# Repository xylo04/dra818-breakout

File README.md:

# DRA818 Breakout

This KiCad project is a breakout board for the DRA818 VHF/UHF transceiver
module. It's extremely simple and designed to be used on a breadboard. It does
incorporate an SMA antenna connector.

This fits the Dorji DRA818 module, both the UHF and VHF variants, and also the
pin-compatible NiceRF SA818 VHF and UHF modules.

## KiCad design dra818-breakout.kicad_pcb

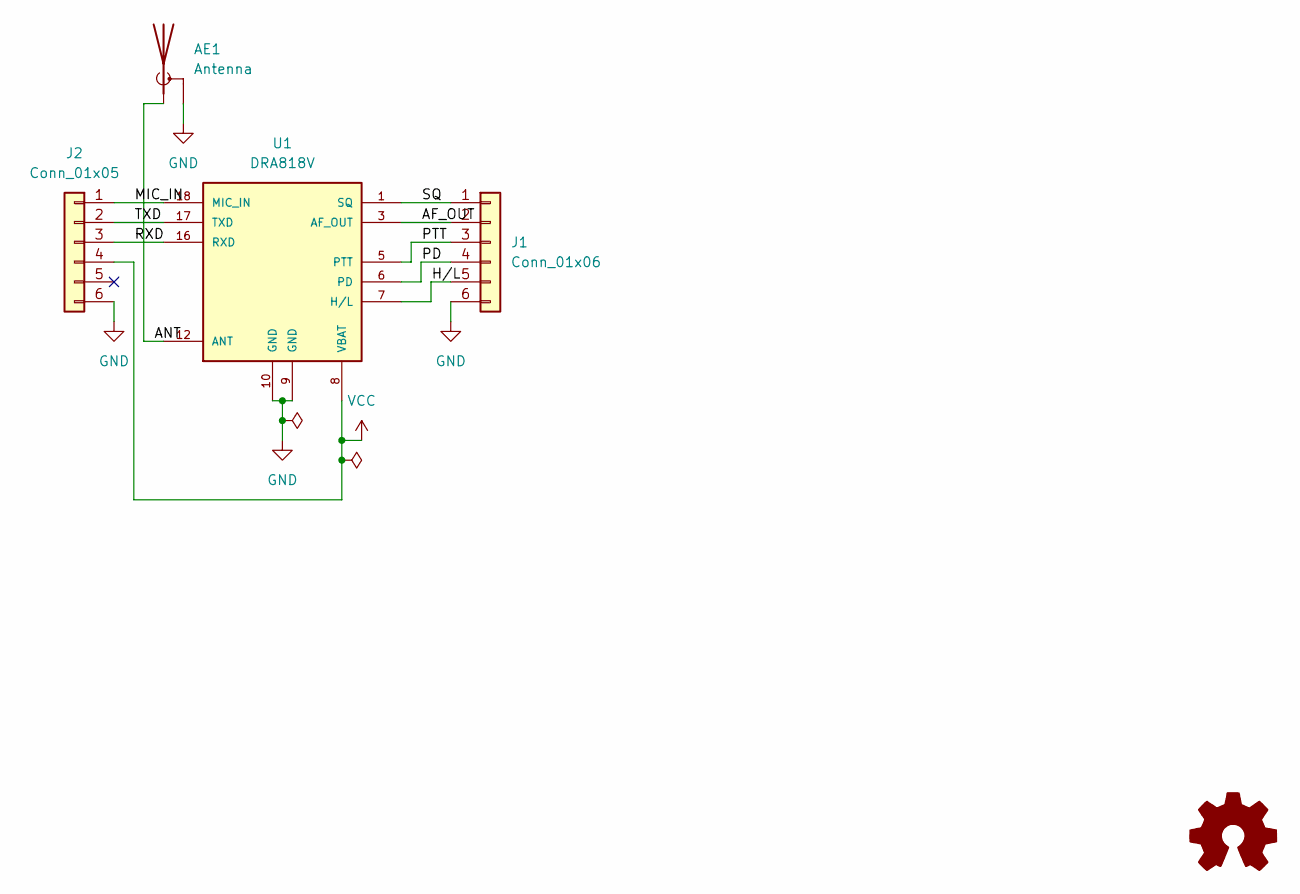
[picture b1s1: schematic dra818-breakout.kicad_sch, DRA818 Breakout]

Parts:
AE1: Antenna; SMA_Molex_73251-1153_EdgeMount_Horizontal
J1: Conn_01x06; PinHeader_1x06_P2.54mm_Vertical
J2: Conn_01x05; PinHeader_1x06_P2.54mm_Vertical
SYM1: Logo_Open_Hardware_Small; OSHW-Logo2_7.3x6mm_SilkScreen
U1: DRA818V; DORJI_DRA818V; PART_REV 1.23

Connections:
/AF_OUT: J1.2, U1.3 (AF_OUT)
/ANT: AE1.1 (A), U1.12 (ANT)
/H/L: J1.5, U1.7 (H/L)
/MIC_IN: J2.1, U1.18 (MIC_IN)
/PD: J1.4, U1.6 (PD)
/PTT: J1.3, U1.5 (PTT)
/RXD: J2.3, U1.16 (RXD)
/SQ: J1.1, U1.1 (SQ)
/TXD: J2.2, U1.17 (TXD)
GND: AE1.2 (Shield), J1.6, J2.6, U1.9 (GND), U1.10 (GND)
VCC: J2.4, U1.8 (VBAT)

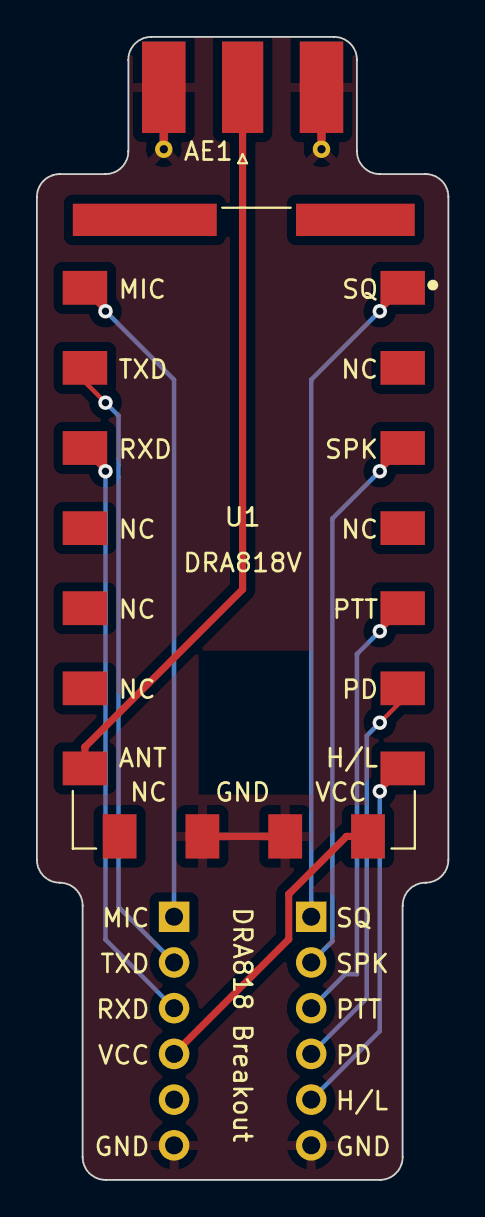
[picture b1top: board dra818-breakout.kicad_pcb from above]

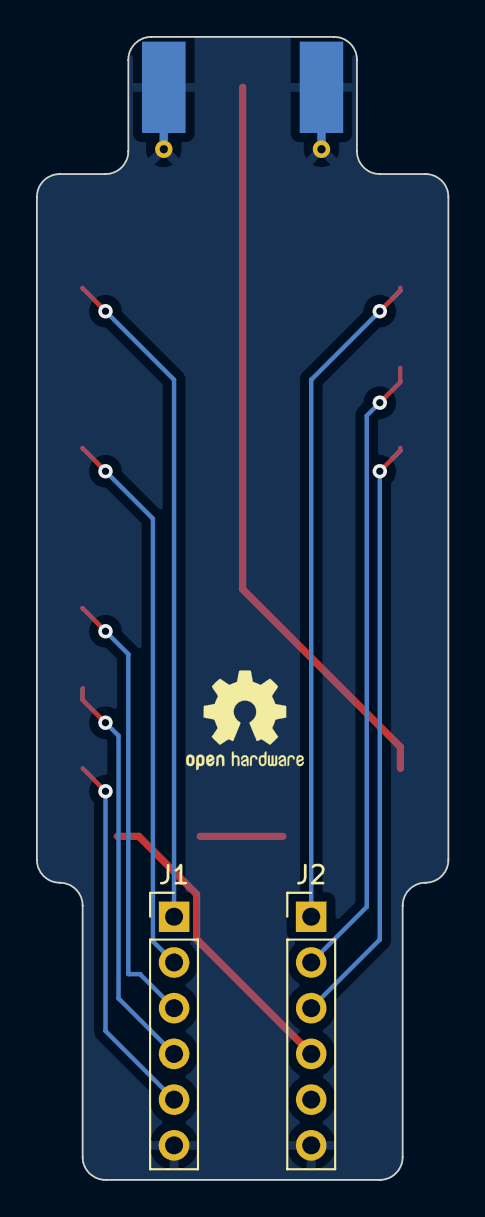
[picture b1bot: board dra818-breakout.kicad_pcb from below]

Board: 2 copper layers, 22.9 x 63.5 mm, 5 parts (3 on the bottom side), 11 nets.

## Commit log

2023-09-17 Add license
2023-09-17 More detail for publishing
2023-09-18 Fix license to not be ShareAlike
    This was my original intent but I published the wrong one.
2023-09-18 Add open hardware logo

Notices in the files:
dra818-breakout.kicad_pcb:
Licensed under CC-BY-4.0
